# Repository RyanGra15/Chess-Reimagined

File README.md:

# Chess-Reimagined

An electronic chess board, that you can play (and lose) against 

## Features

* 64 Hall effect sensors to detect the position of the chess pieces
* LEDs matrix to indicate moves
* 0.96 inch OLED screen
* 3D printed board housing

## How It Works

The board uses Hall effect sensors underneath each square to detect whether a chess piece is present. Each chess piece will have a magnet embedded into its base, allowing the sensor underneath it to detect that a piece is present. Then, the software will take this, and represent it as a 64 bit string, with each bit signifying if there is a piece on the corresponding square. 

By backtracking through prior positions, all the way to the starting position, the ESP32 will be able to determine where each piece is. Then over Wifi, it will call the Stockfish API, get the best move, convert it back to the 64 bit string, and send it back to the Arduino. 

The Arduino will then control the LEDs underneath the board. The two squares involved in the move will light up, showing the player which piece to move and where to move it.

## Electronics

I am using multiplexing-esque approach for both the Hall effect sensors and the LEDs. By feeding 5V to a specified row, and making a specified column GND, I can choose to give power to a specific part. This allows me to control many signals without needing a separate connection for every single component. This keeps the circuit relatively simple and reduces the number of connections needed.

The main electronics are:

* Arduino Mega 2560
* ESP32
* Hall effect sensors
* LEDs
* S8550 PNP transistors
* Resistors
* Magnets
* Wires

The PCB is shown below, along with the schematic and routing diagrams: 

## CAD Model

The board housing will be 3D printed using PLA+. I chose PLA+ because it is cost efficient and is available in many different colors. The board will use a light grey and cold white colour scheme. 

The squares on the chess board have a hole in which the LED can be slotted into, along with a separate inset, wherein a extremely weak magnet can be placed, so that the chess pieces do not repel or attract each other, and instead they attract to the magnets embedded in the base of each square. This also has the added upside that you can flip the board upside down (if that is more your style ;)). See image below:

The chess pieces are also designed digitally and 3D printed, with some inspiration taken from previous chess related projects. 

The different parts will be attached together using hopes, dreams, and a lot of super glue.

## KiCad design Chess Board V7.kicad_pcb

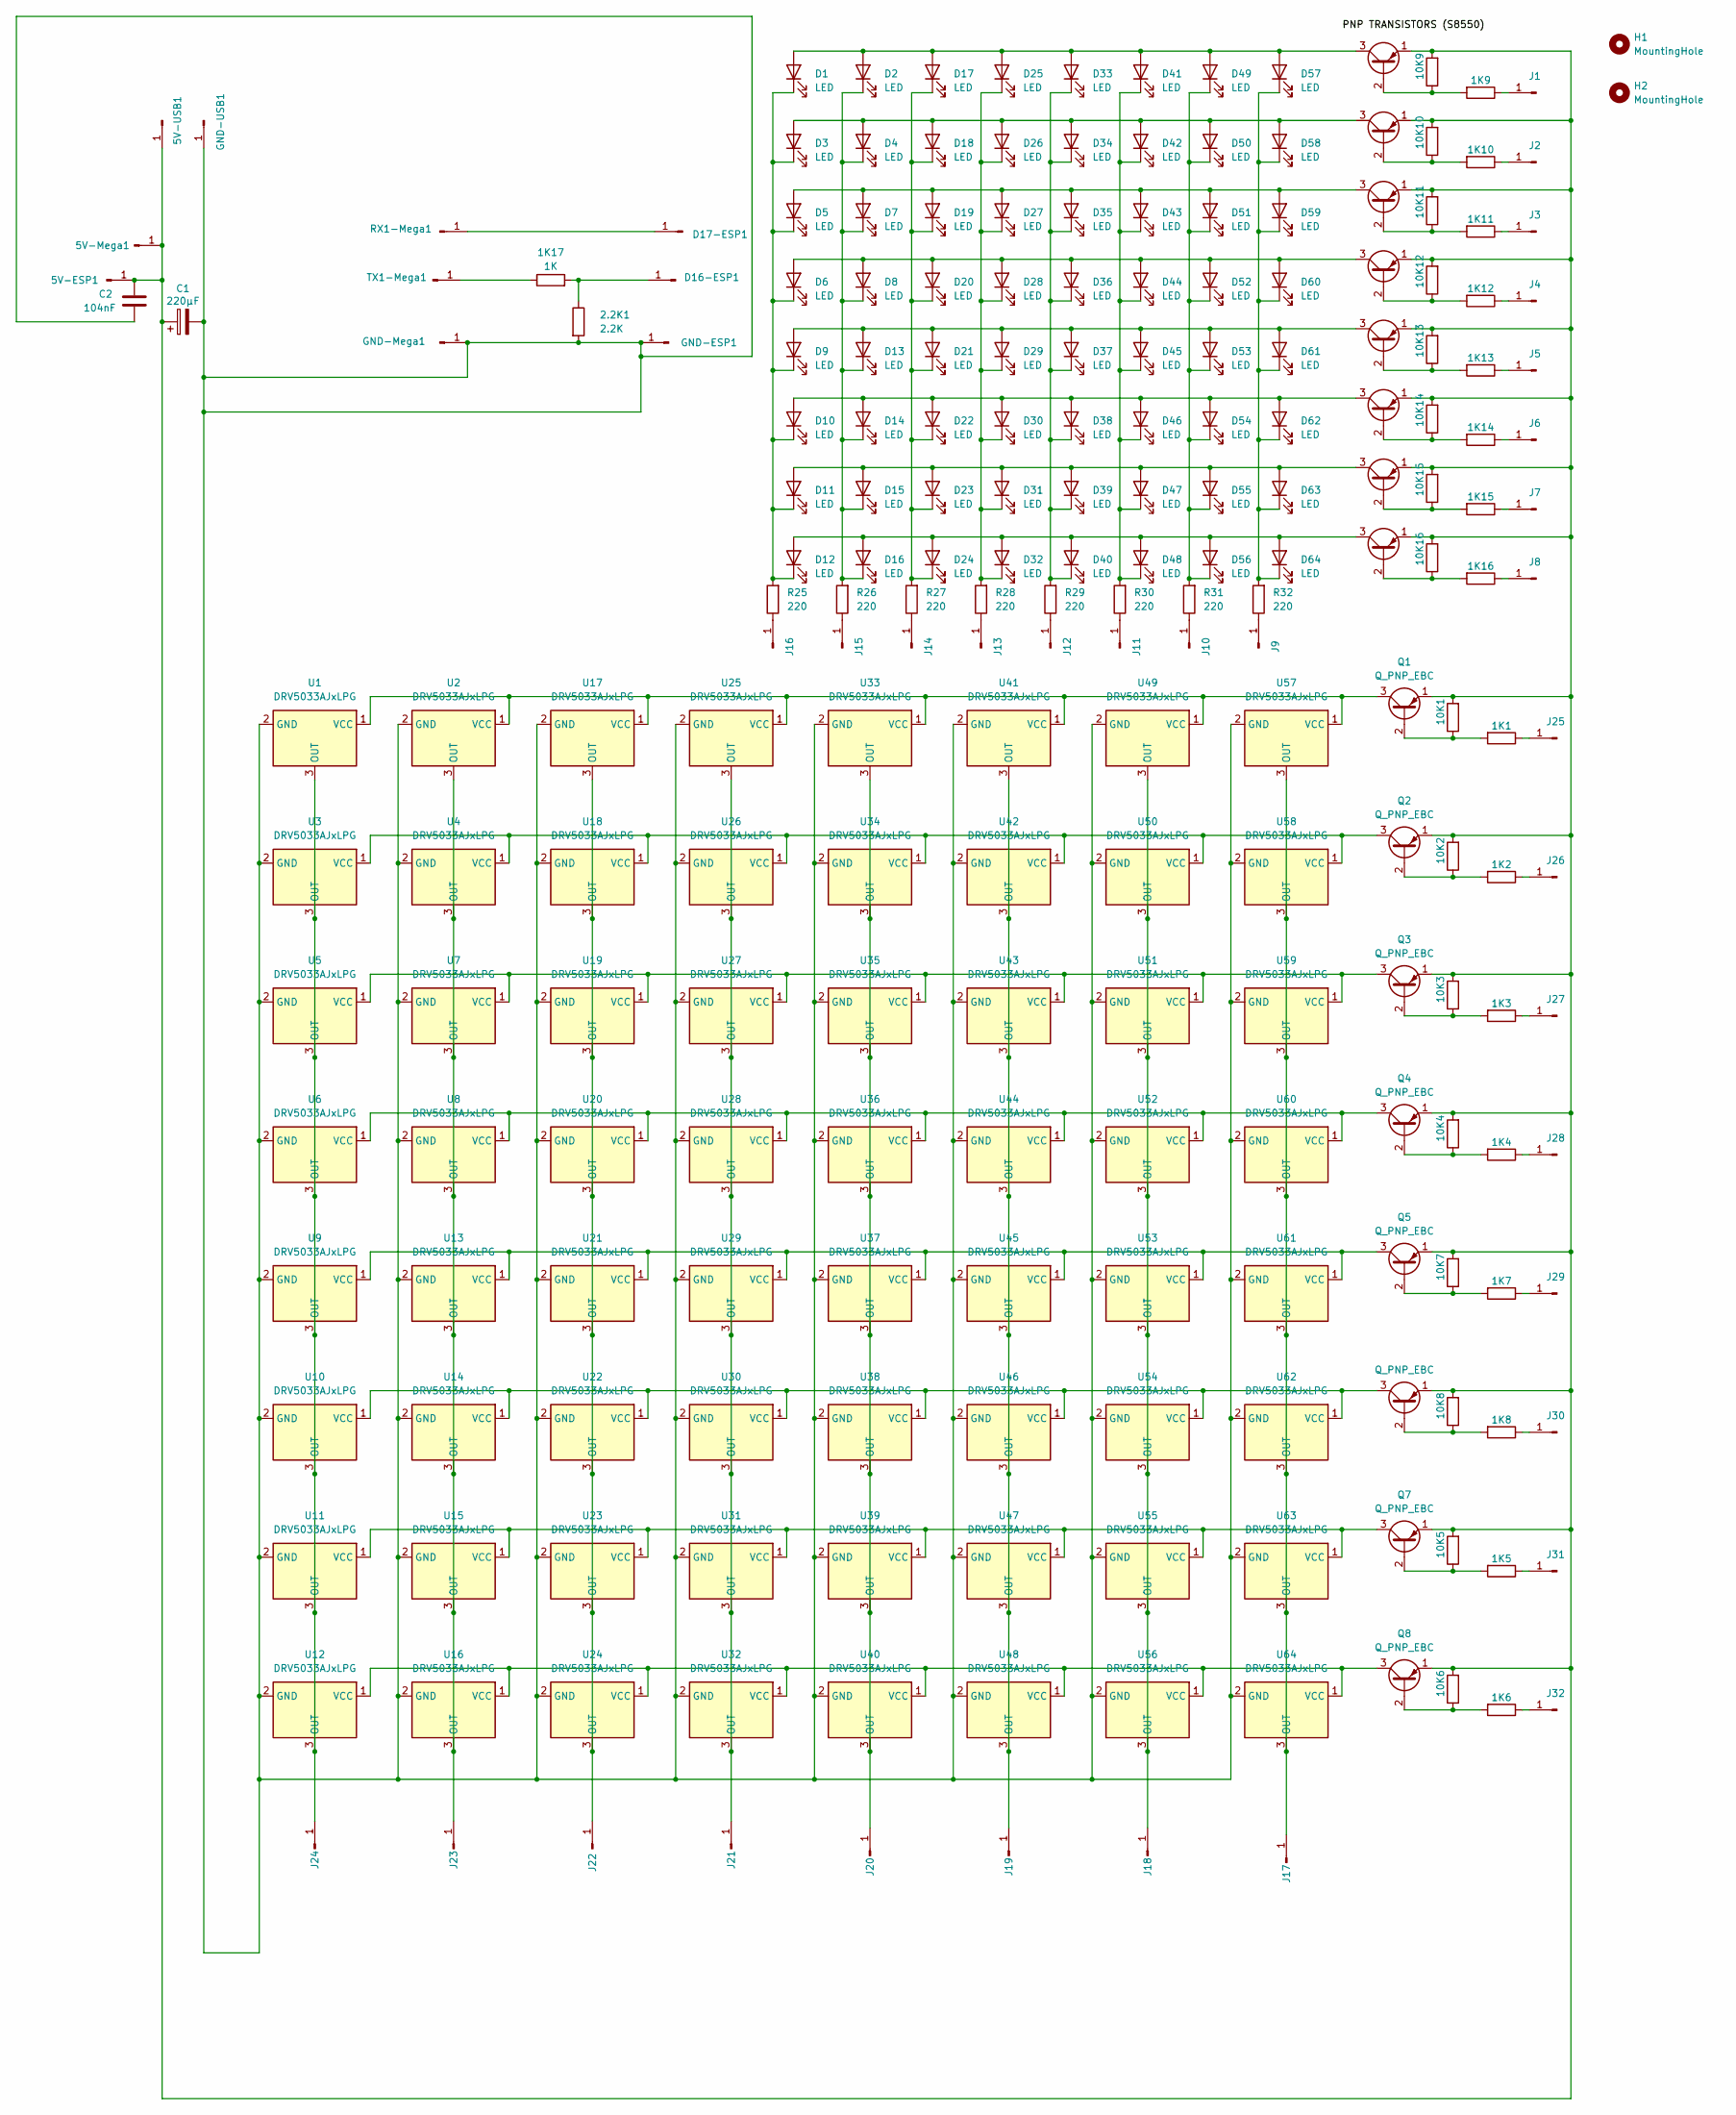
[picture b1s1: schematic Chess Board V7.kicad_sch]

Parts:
1K1, 1K2, 1K3, 1K4, 1K5, 1K6, 1K7, 1K8, 1K9, 1K10, 1K11, 1K12, 1K13, 1K14, 1K15, 1K16, 1K17: 1K; R_Axial_DIN0204_L3.6mm_D1.6mm_P7.62mm_Horizontal
2.2K1: 2.2K; R_Axial_DIN0204_L3.6mm_D1.6mm_P7.62mm_Horizontal
5V-ESP1, 5V-Mega1, 5V-USB1: Conn_01x01_Pin; PinHeader_1x01_P2.54mm_Vertical
10K1, 10K2, 10K3, 10K4, 10K5, 10K6, 10K7, 10K8, 10K9, 10K10, 10K11, 10K12, 10K13, 10K14, 10K15, 10K16: 10K; R_Axial_DIN0204_L3.6mm_D1.6mm_P7.62mm_Horizontal
C1: 220µF; CP_Radial_D6.3mm_P2.50mm
C2: 104nF; C_Disc_D5.0mm_W2.5mm_P2.50mm
D1, D2, D3, D4, D5, D6, D7, D8, D9, D10, D11, D12, D13, D14, D15, D16, D17, D18, D19, D20, D21, D22, D23, D24, D25, D26, D27, D28, D29, D30, D31, D32, D33, D34, D35, D36, D37, D38, D39, D40, D41, D42, D43, D44, D45, D46, D47, D48, D49, D50, D51, D52, D53, D54, D55, D56, D57, D58, D59, D60, D61, D62, D63, D64: LED; LED_D3.0mm_FlatTop
D16-ESP1, D17-ESP1: Conn_01x01_Pin; PinHeader_1x01_P2.54mm_Vertical
GND-ESP1: Conn_01x01_Pin; PinHeader_1x01_P2.54mm_Vertical
GND-Mega1: Conn_01x01_Pin; PinHeader_1x01_P2.54mm_Vertical
GND-USB1: Conn_01x01_Pin; PinHeader_1x01_P2.54mm_Vertical
H1, H2: MountingHole; MountingHole_2.7mm
J1, J2, J3, J4, J5, J6, J7, J8, J9, J10, J11, J12, J13, J14, J15, J16, J17, J18, J19, J20, J21, J22, J23, J24, J25, J26, J27, J28, J29, J30, J31, J32: Conn_01x01_Pin; PinHeader_1x01_P2.54mm_Vertical
Q1, Q2, Q3, Q4, Q5, Q6, Q7, Q8, Q9, Q10, Q11, Q12, Q13, Q14, Q15, Q16: Q_PNP_EBC; TO-92_Inline_Wide
R25, R26, R27, R28, R29, R30, R31, R32: 220; R_Axial_DIN0204_L3.6mm_D1.6mm_P7.62mm_Horizontal
RX1-Mega1: Conn_01x01_Pin; PinHeader_1x01_P2.54mm_Vertical
TX1-Mega1: Conn_01x01_Pin; PinHeader_1x01_P2.54mm_Vertical
U1, U2, U3, U4, U5, U6, U7, U8, U9, U10, U11, U12, U13, U14, U15, U16, U17, U18, U19, U20, U21, U22, U23, U24, U25, U26, U27, U28, U29, U30, U31, U32, U33, U34, U35, U36, U37, U38, U39, U40, U41, U42, U43, U44, U45, U46, U47, U48, U49, U50, U51, U52, U53, U54, U55, U56, U57, U58, U59, U60, U61, U62, U63, U64: DRV5033AJxLPG; TO-92_Inline_Wide

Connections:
unnamed 0: 5V-ESP1.1, 5V-Mega1.1, 5V-USB1.1, 10K1.2, 10K2.2, 10K3.2, 10K4.2, 10K5.2, 10K6.2, 10K7.2, 10K8.2, 10K9.2, 10K10.2, 10K11.2, 10K12.2, 10K13.2, 10K14.2, 10K15.2, 10K16.2, C1.1, C2.1, Q1.1 (E), Q2.1 (E), Q3.1 (E), Q4.1 (E), Q5.1 (E), Q6.1 (E), Q7.1 (E), Q8.1 (E), Q9.1 (E), Q10.1 (E), Q11.1 (E), Q12.1 (E), Q13.1 (E), Q14.1 (E), Q15.1 (E), Q16.1 (E); also elsewhere on the board
unnamed: D1.2 (A), D2.2 (A), D17.2 (A), D25.2 (A), D33.2 (A), D41.2 (A), D49.2 (A), D57.2 (A), Q9.3 (C)
unnamed: D1.1 (K), D3.1 (K), D5.1 (K), D6.1 (K), D9.1 (K), D10.1 (K), D11.1 (K), D12.1 (K), R25.2
unnamed: D10.2 (A), D14.2 (A), D22.2 (A), D30.2 (A), D38.2 (A), D46.2 (A), D54.2 (A), D62.2 (A), Q14.3 (C)
unnamed: D11.2 (A), D15.2 (A), D23.2 (A), D31.2 (A), D39.2 (A), D47.2 (A), D55.2 (A), D63.2 (A), Q15.3 (C)
unnamed: D12.2 (A), D16.2 (A), D24.2 (A), D32.2 (A), D40.2 (A), D48.2 (A), D56.2 (A), D64.2 (A), Q16.3 (C)
unnamed: D9.2 (A), D13.2 (A), D21.2 (A), D29.2 (A), D37.2 (A), D45.2 (A), D53.2 (A), D61.2 (A), Q13.3 (C)
unnamed: D2.1 (K), D4.1 (K), D7.1 (K), D8.1 (K), D13.1 (K), D14.1 (K), D15.1 (K), D16.1 (K), R26.2
unnamed: 1K17.2, 2.2K1.1, D16-ESP1.1
unnamed: D17-ESP1.1, RX1-Mega1.1
unnamed: D17.1 (K), D18.1 (K), D19.1 (K), D20.1 (K), D21.1 (K), D22.1 (K), D23.1 (K), D24.1 (K), R27.2
unnamed: D3.2 (A), D4.2 (A), D18.2 (A), D26.2 (A), D34.2 (A), D42.2 (A), D50.2 (A), D58.2 (A), Q10.3 (C)
unnamed: D5.2 (A), D7.2 (A), D19.2 (A), D27.2 (A), D35.2 (A), D43.2 (A), D51.2 (A), D59.2 (A), Q11.3 (C)
unnamed: D6.2 (A), D8.2 (A), D20.2 (A), D28.2 (A), D36.2 (A), D44.2 (A), D52.2 (A), D60.2 (A), Q12.3 (C)
unnamed: D25.1 (K), D26.1 (K), D27.1 (K), D28.1 (K), D29.1 (K), D30.1 (K), D31.1 (K), D32.1 (K), R28.2
unnamed: D33.1 (K), D34.1 (K), D35.1 (K), D36.1 (K), D37.1 (K), D38.1 (K), D39.1 (K), D40.1 (K), R29.2
unnamed: D41.1 (K), D42.1 (K), D43.1 (K), D44.1 (K), D45.1 (K), D46.1 (K), D47.1 (K), D48.1 (K), R30.2
unnamed: D49.1 (K), D50.1 (K), D51.1 (K), D52.1 (K), D53.1 (K), D54.1 (K), D55.1 (K), D56.1 (K), R31.2
unnamed: D57.1 (K), D58.1 (K), D59.1 (K), D60.1 (K), D61.1 (K), D62.1 (K), D63.1 (K), D64.1 (K), R32.2
unnamed 19: 2.2K1.2, C1.2, C2.2, GND-ESP1.1, GND-Mega1.1, GND-USB1.1, U1.2 (GND), U2.2 (GND), U3.2 (GND), U4.2 (GND), U5.2 (GND), U6.2 (GND), U7.2 (GND), U8.2 (GND), U9.2 (GND), U10.2 (GND), U11.2 (GND), U12.2 (GND), U13.2 (GND), U14.2 (GND), U15.2 (GND), U16.2 (GND), U17.2 (GND), U18.2 (GND), U19.2 (GND), U20.2 (GND), U21.2 (GND), U22.2 (GND), U23.2 (GND), U24.2 (GND), U25.2 (GND), U26.2 (GND), U27.2 (GND), U28.2 (GND), U29.2 (GND), U30.2 (GND), U31.2 (GND), U32.2 (GND), U33.2 (GND), U34.2 (GND), U35.2 (GND), U36.2 (GND), U37.2 (GND), U38.2 (GND), U39.2 (GND), U40.2 (GND), U41.2 (GND), U42.2 (GND), U43.2 (GND), U44.2 (GND), U45.2 (GND), U46.2 (GND), U47.2 (GND), U48.2 (GND), U49.2 (GND), U50.2 (GND), U51.2 (GND), U52.2 (GND), U53.2 (GND), U54.2 (GND), U55.2 (GND), U56.2 (GND), U57.2 (GND), U58.2 (GND), U59.2 (GND), U60.2 (GND), U61.2 (GND), U62.2 (GND), U63.2 (GND), U64.2 (GND); also elsewhere on the board
unnamed: 1K9.1, J1.1
unnamed: 1K10.1, J2.1
unnamed: 1K11.1, J3.1
unnamed: 1K12.1, J4.1
unnamed: 1K13.1, J5.1
unnamed: 1K14.1, J6.1
unnamed: 1K15.1, J7.1
unnamed: 1K16.1, J8.1
unnamed: J9.1, R32.1
unnamed: J10.1, R31.1
unnamed: J11.1, R30.1
unnamed: J12.1, R29.1
unnamed: J13.1, R28.1
unnamed: J14.1, R27.1
unnamed: J15.1, R26.1
unnamed: J16.1, R25.1
unnamed: J17.1, U57.3 (OUT), U58.3 (OUT), U59.3 (OUT), U60.3 (OUT), U61.3 (OUT), U62.3 (OUT), U63.3 (OUT), U64.3 (OUT)
unnamed: J18.1, U49.3 (OUT), U50.3 (OUT), U51.3 (OUT), U52.3 (OUT), U53.3 (OUT), U54.3 (OUT), U55.3 (OUT), U56.3 (OUT)
unnamed: J19.1, U41.3 (OUT), U42.3 (OUT), U43.3 (OUT), U44.3 (OUT), U45.3 (OUT), U46.3 (OUT), U47.3 (OUT), U48.3 (OUT)
unnamed: J20.1, U33.3 (OUT), U34.3 (OUT), U35.3 (OUT), U36.3 (OUT), U37.3 (OUT), U38.3 (OUT), U39.3 (OUT), U40.3 (OUT)
unnamed: J21.1, U25.3 (OUT), U26.3 (OUT), U27.3 (OUT), U28.3 (OUT), U29.3 (OUT), U30.3 (OUT), U31.3 (OUT), U32.3 (OUT)
unnamed: J22.1, U17.3 (OUT), U18.3 (OUT), U19.3 (OUT), U20.3 (OUT), U21.3 (OUT), U22.3 (OUT), U23.3 (OUT), U24.3 (OUT)
unnamed: J23.1, U2.3 (OUT), U4.3 (OUT), U7.3 (OUT), U8.3 (OUT), U13.3 (OUT), U14.3 (OUT), U15.3 (OUT), U16.3 (OUT)
unnamed: J24.1, U1.3 (OUT), U3.3 (OUT), U5.3 (OUT), U6.3 (OUT), U9.3 (OUT), U10.3 (OUT), U11.3 (OUT), U12.3 (OUT)
unnamed: 1K1.1, J25.1
unnamed: 1K2.1, J26.1
unnamed: 1K3.1, J27.1
unnamed: 1K4.1, J28.1
unnamed: 1K7.1, J29.1
unnamed: 1K8.1, J30.1
unnamed: 1K5.1, J31.1
unnamed: 1K6.1, J32.1
unnamed: 1K1.2, 10K1.1, Q1.2 (B)
unnamed: Q1.3 (C), U1.1 (VCC), U2.1 (VCC), U17.1 (VCC), U25.1 (VCC), U33.1 (VCC), U41.1 (VCC), U49.1 (VCC), U57.1 (VCC)
unnamed: 1K2.2, 10K2.1, Q2.2 (B)
unnamed: Q2.3 (C), U3.1 (VCC), U4.1 (VCC), U18.1 (VCC), U26.1 (VCC), U34.1 (VCC), U42.1 (VCC), U50.1 (VCC), U58.1 (VCC)
unnamed: 1K3.2, 10K3.1, Q3.2 (B)
unnamed: Q3.3 (C), U5.1 (VCC), U7.1 (VCC), U19.1 (VCC), U27.1 (VCC), U35.1 (VCC), U43.1 (VCC), U51.1 (VCC), U59.1 (VCC)
unnamed: 1K4.2, 10K4.1, Q4.2 (B)
unnamed: Q4.3 (C), U6.1 (VCC), U8.1 (VCC), U20.1 (VCC), U28.1 (VCC), U36.1 (VCC), U44.1 (VCC), U52.1 (VCC), U60.1 (VCC)
unnamed: 1K7.2, 10K7.1, Q5.2 (B)
unnamed: Q5.3 (C), U9.1 (VCC), U13.1 (VCC), U21.1 (VCC), U29.1 (VCC), U37.1 (VCC), U45.1 (VCC), U53.1 (VCC), U61.1 (VCC)
unnamed: 1K8.2, 10K8.1, Q6.2 (B)
unnamed: Q6.3 (C), U10.1 (VCC), U14.1 (VCC), U22.1 (VCC), U30.1 (VCC), U38.1 (VCC), U46.1 (VCC), U54.1 (VCC), U62.1 (VCC)
unnamed: 1K5.2, 10K5.1, Q7.2 (B)
unnamed: Q7.3 (C), U11.1 (VCC), U15.1 (VCC), U23.1 (VCC), U31.1 (VCC), U39.1 (VCC), U47.1 (VCC), U55.1 (VCC), U63.1 (VCC)
unnamed: 1K6.2, 10K6.1, Q8.2 (B)
unnamed: Q8.3 (C), U12.1 (VCC), U16.1 (VCC), U24.1 (VCC), U32.1 (VCC), U40.1 (VCC), U48.1 (VCC), U56.1 (VCC), U64.1 (VCC)
unnamed: 1K9.2, 10K9.1, Q9.2 (B)
unnamed: 1K10.2, 10K10.1, Q10.2 (B)
unnamed: 1K11.2, 10K11.1, Q11.2 (B)
unnamed: 1K12.2, 10K12.1, Q12.2 (B)
unnamed: 1K13.2, 10K13.1, Q13.2 (B)
unnamed: 1K14.2, 10K14.1, Q14.2 (B)
unnamed: 1K15.2, 10K15.1, Q15.2 (B)
unnamed: 1K16.2, 10K16.1, Q16.2 (B)
unnamed: 1K17.1, TX1-Mega1.1

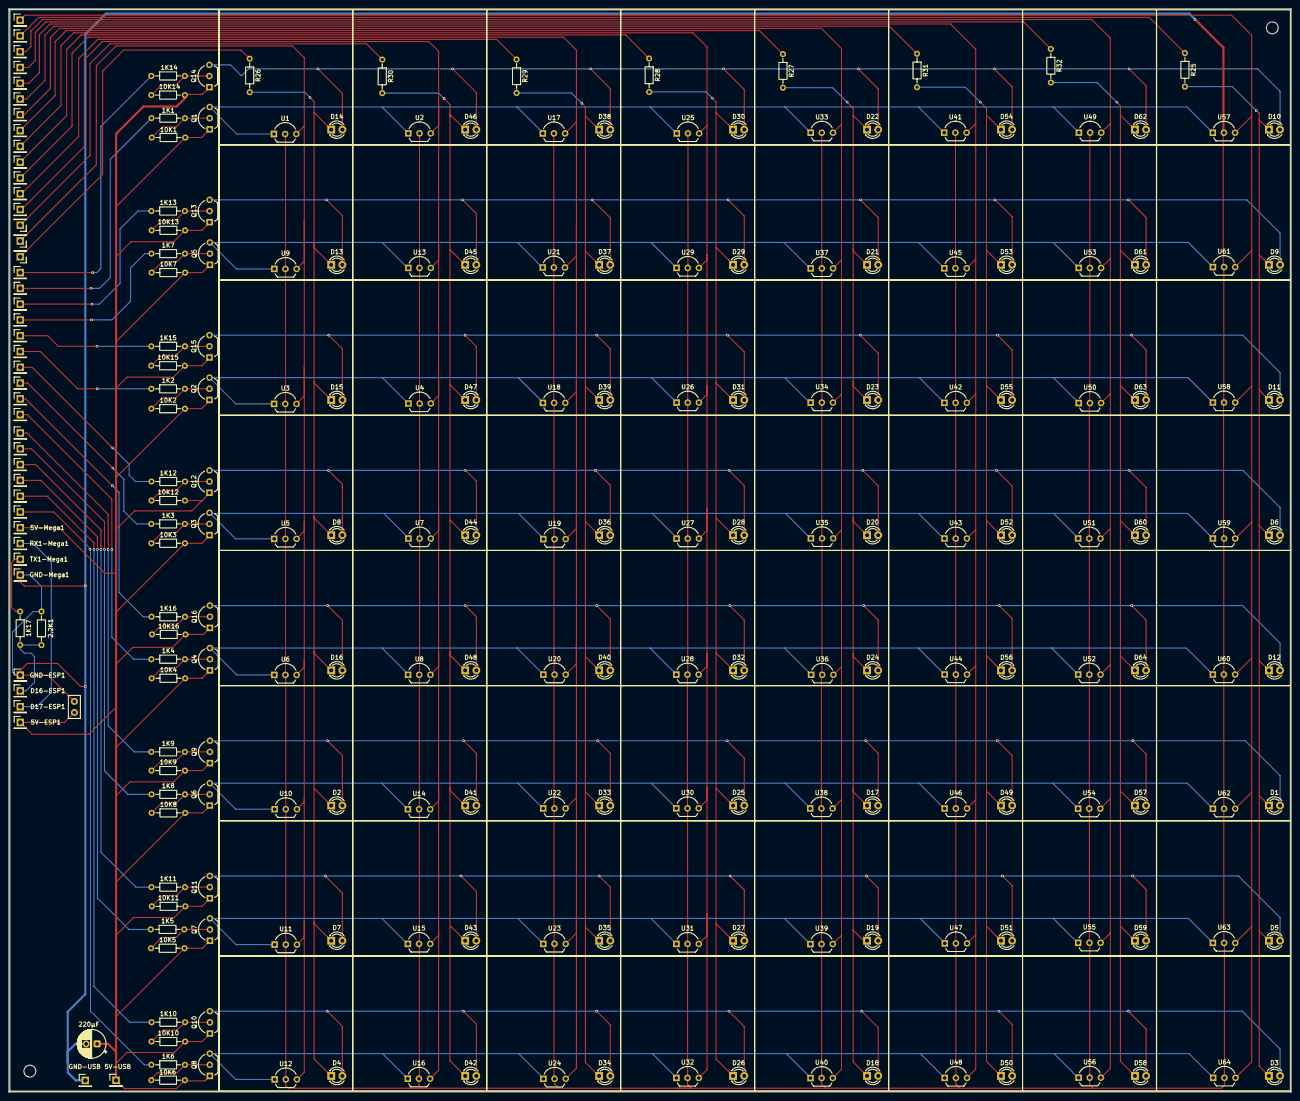
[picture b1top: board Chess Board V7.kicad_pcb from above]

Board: 2 copper layers, 291.5 x 246.2 mm, 232 parts (0 on the bottom side), 77 nets.

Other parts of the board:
5V-USB: Conn_01x01_Pin; PinHeader_1x01_P2.54mm_Vertical
220µF: 220µF; CP_Radial_D6.3mm_P2.50mm
GND-USB: Conn_01x01_Pin; PinHeader_1x01_P2.54mm_Vertical

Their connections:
unnamed 0: 5V-USB.1, 220µF.1; also elsewhere on the board
unnamed 19: 220µF.2, GND-USB.1; also elsewhere on the board
